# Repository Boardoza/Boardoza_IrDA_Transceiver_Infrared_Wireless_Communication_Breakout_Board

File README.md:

# Boardoza IrDA Transceiver Breakout Board

The **Boardoza IrDA Transceiver** is a compact infrared communication breakout board designed for reliable short-range wireless data transfer using modulated infrared light. The board integrates both an infrared transmitter and a demodulating infrared receiver, enabling digital data transmission and reception through a simple TXD/RXD interface. It supports operation with both **3.3V and 5V systems**, making it compatible with a wide range of microcontroller platforms.

The onboard hardware-driven LED indicators provide instant visual feedback for power, transmission, and reception activities, making debugging and communication monitoring extremely convenient during development. With its compact footprint and integrated infrared communication circuitry, this board is ideal for **embedded wireless links, short-range wireless control systems, educational electronics projects, robotics, and custom infrared serial communication applications**.

## [Click here to purchase!](https://www.ozdisan.com/ureticiler/boardoza)

| Front Side | Back Side |
|:---:|:---:|
|  |  |

---

## Key Features

- **38 kHz Infrared Communication:** Supports reliable infrared wireless data transfer using a 38 kHz modulated carrier frequency.
- **Integrated IR Receiver Circuit:** Features a built-in demodulating infrared receiver for clean and stable digital signal output.
- **Wide Voltage Compatibility:** Operates seamlessly with both 3.3V and 5V microcontroller platforms.
- **Real-Time Status Indicators:** Dedicated hardware LEDs provide instant visual feedback for data reception (D2) and data transmission (D3) activity.  
- **Simple Digital TXD/RXD Interface:** Provides straightforward MCU communication through TXD input and RXD output pins.
- **TX Echo Functionality:** Transmitted data is internally echoed to the RX output for easier debugging and monitoring.

---

## Technical Specifications

**Model:** IrDA Transceiver   
**Manufactorer:** Boardoza  
**Functions:** Infrared Data Transmitter & Receiver  
**Input Voltage:** 3.3V – 5V  
**Communication Type:** Asynchronous Serial  
**Carrier Frequency:** 38 kHz  
**Maximum Data Rate:** Up to 1250 bps  
**Infrared LED Wavelength:** 940 nm  
**Transmission Range (3.3V):** Up to 430 cm  
**Transmission Range (5V):** Up to 600 cm  
**Indicator LEDs:** RX (Yellow), TX (Green)  
**Receiver Type:** Demodulating IR Receiver Module  
**Operating Temperature:** -40°C to +85°C  
**Board Dimensions:** 20mm x 20mm  

> Warning: The TXD pin directly controls the IR transmitter stage and must only be driven with short data pulses. Applying a continuous HIGH level to TXD may cause excessive current through the IR LED/driver circuit and can permanently damage the board.

---

## Board Pinout

### ( J1 ) Communication Connector

| Pin Number | Pin Name | Description |
|:---:|:---:|---|
| 1 | VCC | Power Supply Input |
| 2 | RXD | Data Receive Output |
| 3 | TXD | Data Transmit Input |
| 4 | GND | Ground |

---

## Board Dimensions

---

## Step Files

[Boardoza IrDA Transceiver.step](./assets/IrDA%20Transceiver%20Step.step)

---

## Datasheet

[VSMB10940 Datasheet.pdf](./assets/VSMB10940%20Datasheet.pdf)

[IR Receiver Module Datasheet.pdf](./assets/DMO-0000008%20Datasheet.pdf)

---

## Version History

- V1.0.0 - Initial Release

---

## Support

- If you have any questions or need support, please contact support@boardoza.com

---

## **License**

This repository contains both hardware and software components:

### **Hardware Design**

[![CC BY-SA 4.0][cc-by-sa-shield]][cc-by-sa]

All hardware design files are licensed under [Creative Commons Attribution-ShareAlike 4.0 International License][cc-by-sa].

[cc-by-sa]: http://creativecommons.org/licenses/by-sa/4.0/
[cc-by-sa-shield]: https://img.shields.io/badge/License-CC%20BY--SA%204.0-lightgrey.svg

### **Software/Firmware**

[![BSD-3-Clause][bsd-shield]][bsd]

All software and firmware are licensed under [BSD 3-Clause License][bsd].

[bsd]: https://opensource.org/licenses/BSD-3-Clause
[bsd-shield]: https://img.shields.io/badge/License-BSD%203--Clause-blue.svg

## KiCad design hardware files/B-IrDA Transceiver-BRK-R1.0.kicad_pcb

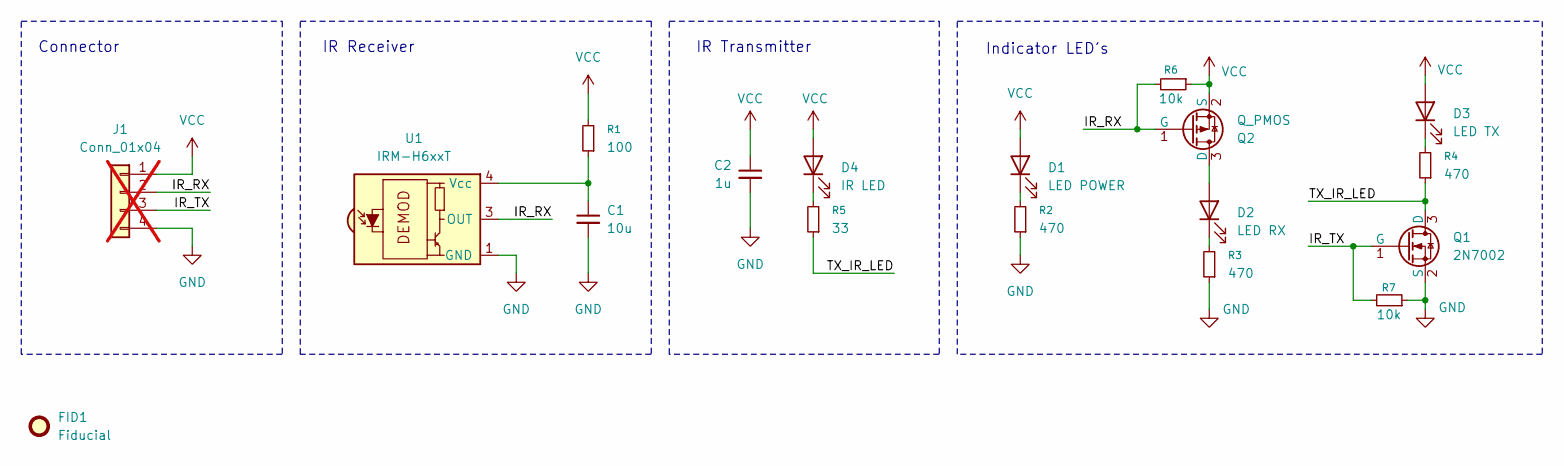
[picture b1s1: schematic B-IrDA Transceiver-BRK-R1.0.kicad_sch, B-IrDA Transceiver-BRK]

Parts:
C1: 10u; C_0603_1608Metric; MPN CL10A106KQ8NNNC
C2: 1u; C_0603_1608Metric; MPN CL10B105KO8NNNC
D1: LED POWER; LED_0603_1608Metric; MPN LTST-C191KRKT
D2: LED RX; LED_0603_1608Metric; MPN LTST-C191KSKT
D3: LED TX; LED_0603_1608Metric; MPN LTST-C191KGKT
D4: IR LED; VSMB10940; MPN VSMB10940
FID1: Fiducial; Fiducial_0.5mm_Mask1mm
J1: Conn_01x04; JST_XH_B4B-XH-A_1x04_P2.50mm_Vertical; MPN L-KLS1-2.50-04-SB; not fitted
Q1: 2N7002; SOT-23; MPN 2N7002_R1_00001
Q2: Q_PMOS; SOT-23; MPN BSS84-HT
R1: 100; R_0603_1608Metric; MPN 0603SAJ0101T5E
R2, R3, R4: 470; R_0603_1608Metric; MPN 0603SAJ0471T5E
R5: 33; R_0603_1608Metric; MPN 0603SAJ0330T5E
R6, R7: 10k; R_0603_1608Metric; MPN 0603SAJ0103T5E
U1: IRM-H6xxT; Everlight_IRM-H6xxT; MPN IRM-H638T/TR2

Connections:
/IR_RX: J1.2, Q2.1 (G), R6.2, U1.3 (OUT)
/IR_TX: J1.3, Q1.1 (G), R7.2
/TX_IR_LED: Q1.3 (D), R4.1, R5.1
GND: C1.2, C2.2, J1.4, Q1.2 (S), R2.1, R3.1, R7.1, U1.1 (GND), U1.2 (GND)
unnamed: D1.1 (K), R2.2
unnamed: D2.2 (A), Q2.3 (D)
unnamed: D2.1 (K), R3.2
unnamed: D3.1 (K), R4.2
unnamed: D4.1 (K), R5.2
unnamed: C1.1, R1.1, U1.4 (Vcc)
VCC: C2.1, D1.2 (A), D3.2 (A), D4.2 (A), J1.1, Q2.2 (S), R1.2, R6.1

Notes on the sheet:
IR Receiver
Indicator LED's
Connector
IR Transmitter

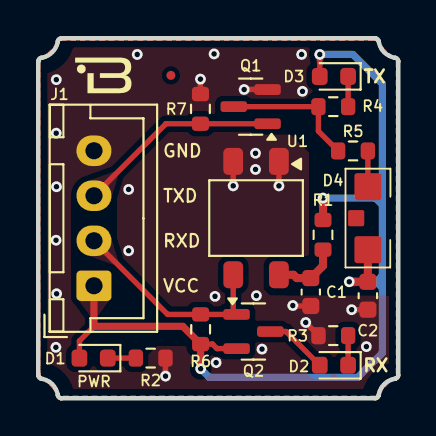
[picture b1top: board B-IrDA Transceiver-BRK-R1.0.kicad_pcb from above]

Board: 2 copper layers, 20.0 x 20.0 mm, 18 parts (0 on the bottom side), 11 nets.
